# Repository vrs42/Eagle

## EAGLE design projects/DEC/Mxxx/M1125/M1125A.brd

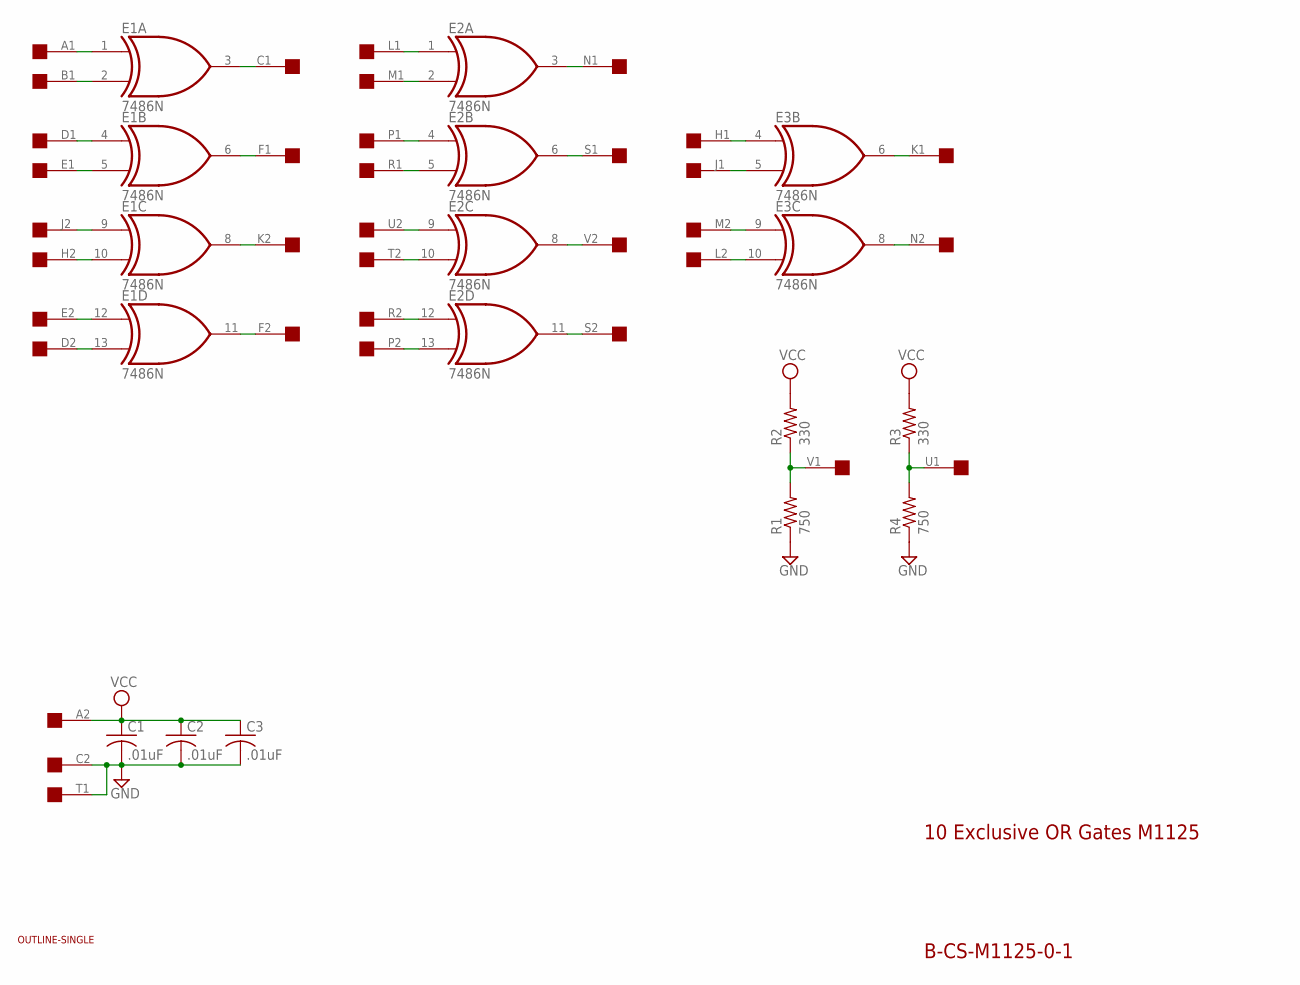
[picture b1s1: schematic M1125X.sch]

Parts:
C1, C2, C3: .01uF; C075-032X103
E1, E2, E3: 7486N; DIL14
R1, R4: 750; 0207/10
R2, R3: 330; 0207/10
U$1: OUTLINE-SINGLE; SINGLE
U$2: SINGLE; EDGE-CON2

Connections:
GND: C1.2, C2.2, C3.2, E1.7 (GND), E2.7 (GND), E3.7 (GND), R1.1, R4.1, U$2.C2, U$2.T1
unnamed: E2.9 (I0), U$2.U2
unnamed: E2.10 (I1), U$2.T2
unnamed: E2.12 (I0), U$2.R2
unnamed: E2.13 (I1), U$2.P2
unnamed: E2.11 (O), U$2.S2
unnamed: E2.8 (O), U$2.V2
unnamed: E1.13 (I1), U$2.D2
unnamed: E1.12 (I0), U$2.E2
unnamed: E1.10 (I1), U$2.H2
unnamed: E1.9 (I0), U$2.J2
unnamed: E1.8 (O), U$2.K2
unnamed: E1.11 (O), U$2.F2
unnamed: E3.10 (I1), U$2.L2
unnamed: E3.9 (I0), U$2.M2
unnamed: E3.8 (O), U$2.N2
unnamed: R1.2, R2.1, U$2.V1
unnamed: R3.1, R4.2, U$2.U1
unnamed: E1.2 (I1), U$2.B1
unnamed: E1.1 (I0), U$2.A1
unnamed: E1.3 (O), U$2.C1
unnamed: E1.6 (O), U$2.F1
unnamed: E1.4 (I0), U$2.D1
unnamed: E1.5 (I1), U$2.E1
unnamed: E3.5 (I1), U$2.J1
unnamed: E3.4 (I0), U$2.H1
unnamed: E3.6 (O), U$2.K1
unnamed: E2.6 (O), U$2.S1
unnamed: E2.3 (O), U$2.N1
unnamed: E2.1 (I0), U$2.L1
unnamed: E2.2 (I1), U$2.M1
unnamed: E2.4 (I0), U$2.P1
unnamed: E2.5 (I1), U$2.R1
VCC: C1.1, C2.1, C3.1, E1.14 (VCC), E2.14 (VCC), E3.14 (VCC), R2.2, R3.2, U$2.A2

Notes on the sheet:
10 Exclusive OR Gates M1125
B-CS-M1125-0-1

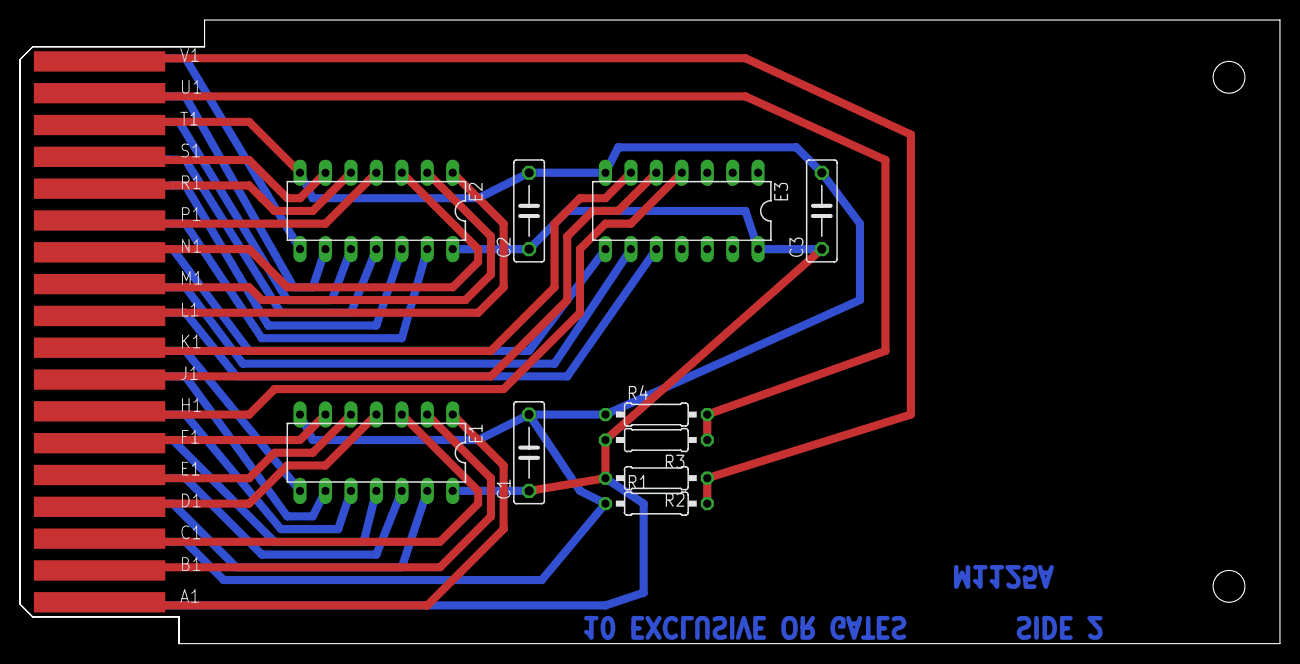
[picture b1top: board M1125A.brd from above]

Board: 2 copper layers, 125.7 x 62.2 mm, 12 parts (0 on the bottom side), 34 nets.

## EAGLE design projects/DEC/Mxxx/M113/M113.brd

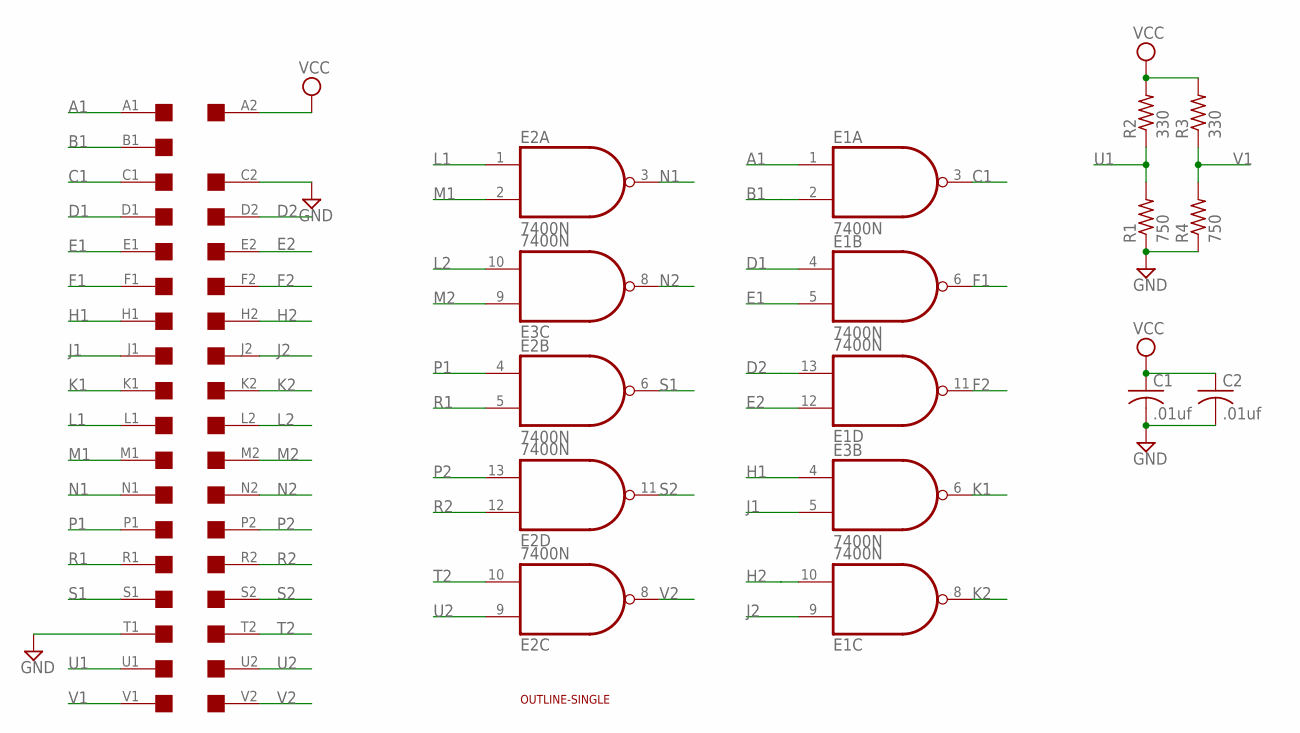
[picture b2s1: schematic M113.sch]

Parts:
C1, C2: .01uf; C050-025X075
E1, E2, E3: 7400N; DIL14
R1, R4: 750; 0207/10
R2, R3: 330; 0207/10
U$1: SINGLE; EDGE-CON2
U$2: OUTLINE-SINGLE; SINGLE

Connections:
A1: E1.1 (I0), U$1.A1
B1: E1.2 (I1), U$1.B1
C1: E1.3 (O), U$1.C1
D1: E1.4 (I0), U$1.D1
D2: E1.13 (I1), U$1.D2
E1: E1.5 (I1), U$1.E1
E2: E1.12 (I0), U$1.E2
F1: E1.6 (O), U$1.F1
F2: E1.11 (O), U$1.F2
GND: C1.2, C2.2, E1.7 (GND), E2.7 (GND), E3.7 (GND), R1.1, R4.1, U$1.C2, U$1.T1
H1: E3.4 (I0), U$1.H1
H2: E1.10 (I1), U$1.H2
J1: E3.5 (I1), U$1.J1
J2: E1.9 (I0), U$1.J2
K1: E3.6 (O), U$1.K1
K2: E1.8 (O), U$1.K2
L1: E2.1 (I0), U$1.L1
L2: E3.10 (I1), U$1.L2
M1: E2.2 (I1), U$1.M1
M2: E3.9 (I0), U$1.M2
N1: E2.3 (O), U$1.N1
N2: E3.8 (O), U$1.N2
P1: E2.4 (I0), U$1.P1
P2: E2.13 (I1), U$1.P2
R1: E2.5 (I1), U$1.R1
R2: E2.12 (I0), U$1.R2
S1: E2.6 (O), U$1.S1
S2: E2.11 (O), U$1.S2
T2: E2.10 (I1), U$1.T2
U1: R1.2, R2.1, U$1.U1
U2: E2.9 (I0), U$1.U2
V1: R3.1, R4.2, U$1.V1
V2: E2.8 (O), U$1.V2
VCC: C1.1, C2.1, E1.14 (VCC), E2.14 (VCC), E3.14 (VCC), R2.2, R3.2, U$1.A2

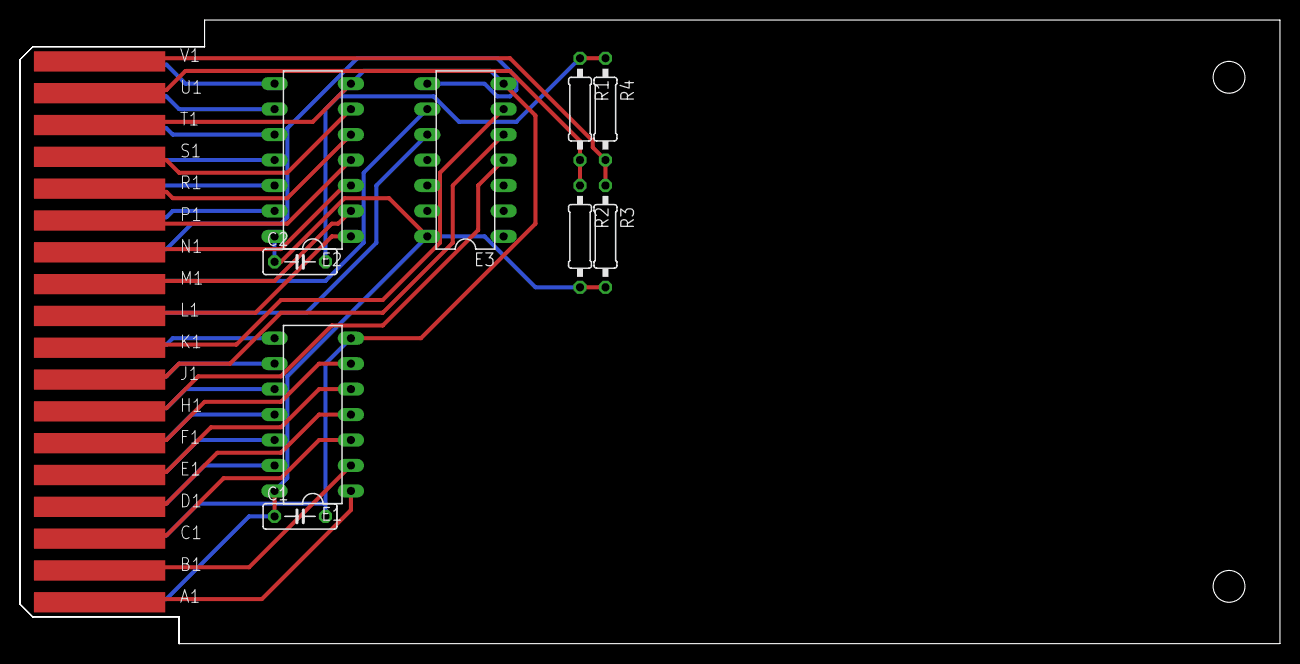
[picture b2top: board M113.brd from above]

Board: 2 copper layers, 125.7 x 62.2 mm, 11 parts (0 on the bottom side), 34 nets.

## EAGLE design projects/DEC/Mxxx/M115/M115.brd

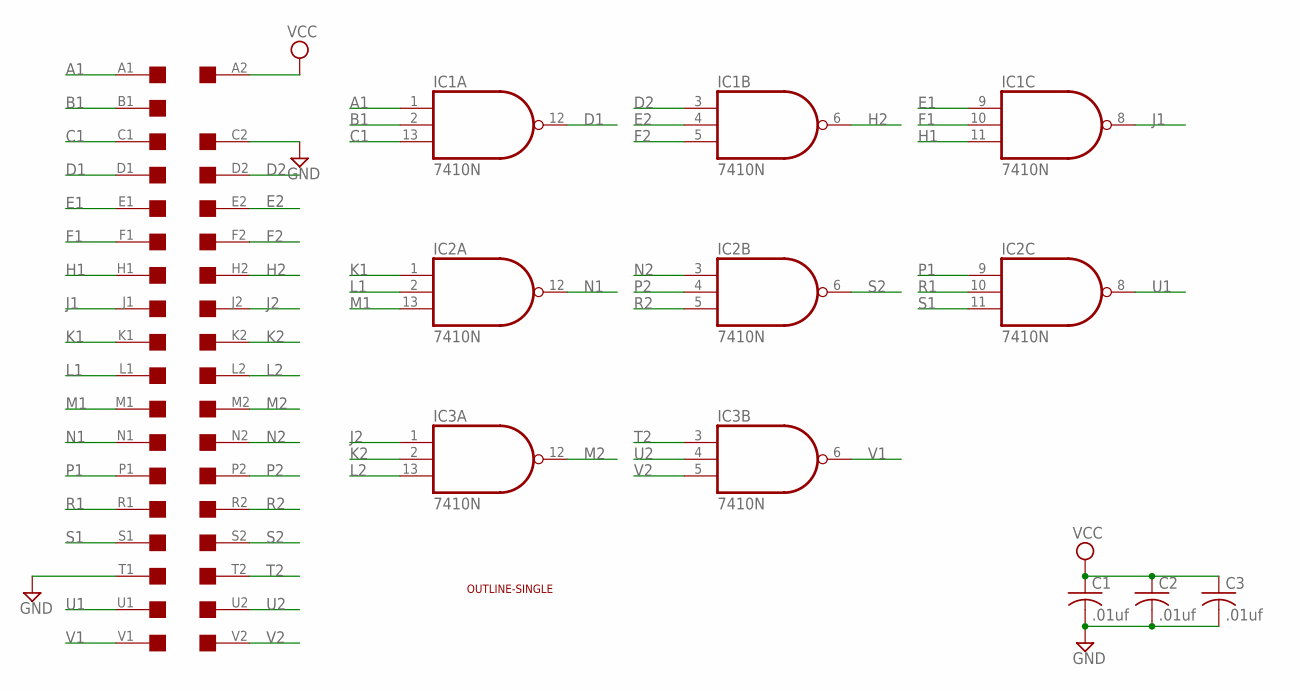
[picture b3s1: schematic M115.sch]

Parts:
C1, C2, C3: .01uf; C050-025X075
IC1, IC2, IC3: 7410N; DIL14
U$1: SINGLE; EDGE-CON2
U$4: OUTLINE-SINGLE; SINGLE

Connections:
A1: IC1.1 (I0), U$1.A1
B1: IC1.2 (I1), U$1.B1
C1: IC1.13 (I2), U$1.C1
D1: IC1.12 (O), U$1.D1
D2: IC1.3 (I0), U$1.D2
E1: IC1.9 (I0), U$1.E1
E2: IC1.4 (I1), U$1.E2
F1: IC1.10 (I1), U$1.F1
F2: IC1.5 (I2), U$1.F2
GND: C1.2, C2.2, C3.2, IC1.7 (GND), IC2.7 (GND), IC3.7 (GND), U$1.C2, U$1.T1
H1: IC1.11 (I2), U$1.H1
H2: IC1.6 (O), U$1.H2
J1: IC1.8 (O), U$1.J1
J2: IC3.1 (I0), U$1.J2
K1: IC2.1 (I0), U$1.K1
K2: IC3.2 (I1), U$1.K2
L1: IC2.2 (I1), U$1.L1
L2: IC3.13 (I2), U$1.L2
M1: IC2.13 (I2), U$1.M1
M2: IC3.12 (O), U$1.M2
N1: IC2.12 (O), U$1.N1
N2: IC2.3 (I0), U$1.N2
P1: IC2.9 (I0), U$1.P1
P2: IC2.4 (I1), U$1.P2
R1: IC2.10 (I1), U$1.R1
R2: IC2.5 (I2), U$1.R2
S1: IC2.11 (I2), U$1.S1
S2: IC2.6 (O), U$1.S2
T2: IC3.3 (I0), U$1.T2
U1: IC2.8 (O), U$1.U1
U2: IC3.4 (I1), U$1.U2
V1: IC3.6 (O), U$1.V1
V2: IC3.5 (I2), U$1.V2
VCC: C1.1, C2.1, C3.1, IC1.14 (VCC), IC2.14 (VCC), IC3.14 (VCC), U$1.A2

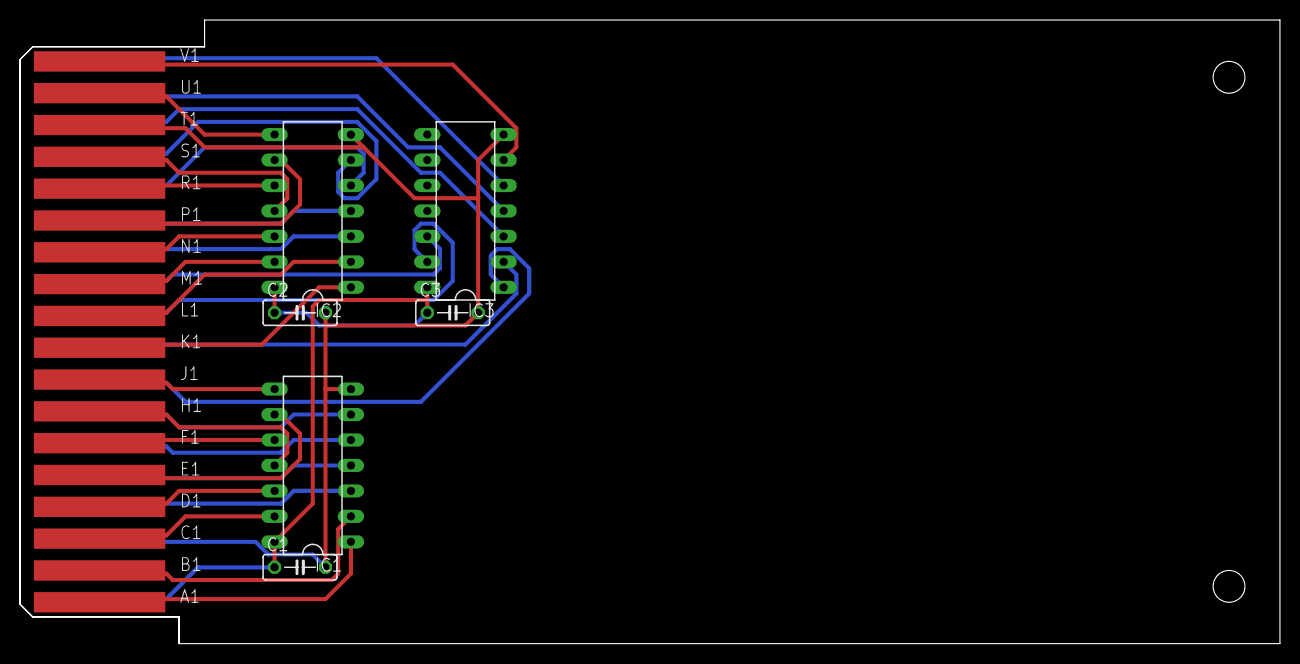
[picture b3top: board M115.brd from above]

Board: 2 copper layers, 125.7 x 62.2 mm, 8 parts (0 on the bottom side), 34 nets.

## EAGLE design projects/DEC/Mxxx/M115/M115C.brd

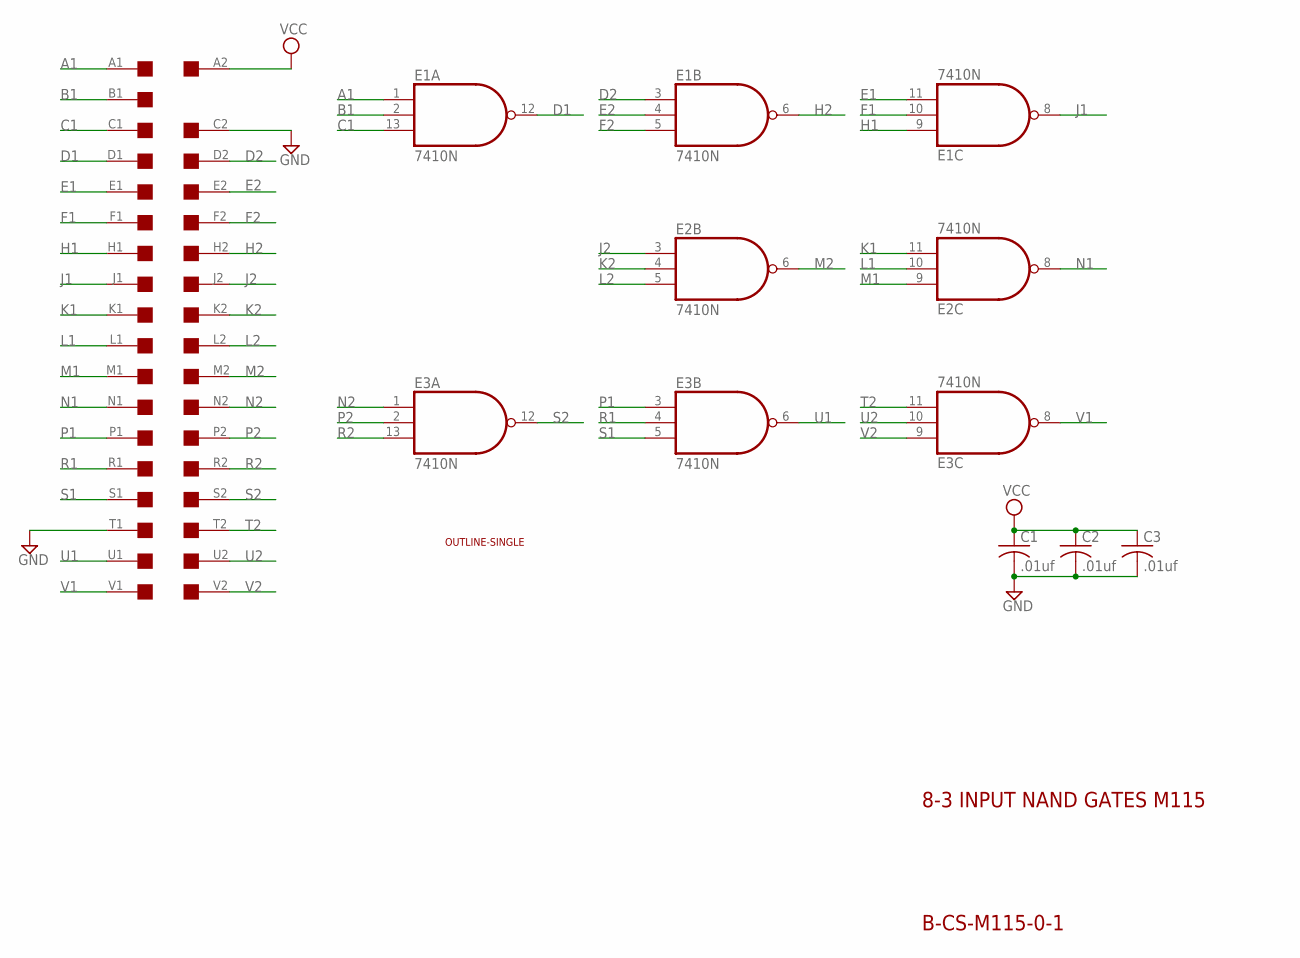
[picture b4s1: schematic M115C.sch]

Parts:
C1, C2, C3: .01uf; C050-025X075
E1, E2, E3: 7410N; DIL14
U$1: SINGLE; EDGE-CON2
U$4: OUTLINE-SINGLE; SINGLE

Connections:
A1: E1.1 (I0), U$1.A1
B1: E1.2 (I1), U$1.B1
C1: E1.13 (I2), U$1.C1
D1: E1.12 (O), U$1.D1
D2: E1.3 (I0), U$1.D2
E1: E1.11 (I2), U$1.E1
E2: E1.4 (I1), U$1.E2
F1: E1.10 (I1), U$1.F1
F2: E1.5 (I2), U$1.F2
GND: C1.2, C2.2, C3.2, E1.7 (GND), E2.7 (GND), E3.7 (GND), U$1.C2, U$1.T1
H1: E1.9 (I0), U$1.H1
H2: E1.6 (O), U$1.H2
J1: E1.8 (O), U$1.J1
J2: E2.3 (I0), U$1.J2
K1: E2.11 (I2), U$1.K1
K2: E2.4 (I1), U$1.K2
L1: E2.10 (I1), U$1.L1
L2: E2.5 (I2), U$1.L2
M1: E2.9 (I0), U$1.M1
M2: E2.6 (O), U$1.M2
N1: E2.8 (O), U$1.N1
N2: E3.1 (I0), U$1.N2
P1: E3.3 (I0), U$1.P1
P2: E3.2 (I1), U$1.P2
R1: E3.4 (I1), U$1.R1
R2: E3.13 (I2), U$1.R2
S1: E3.5 (I2), U$1.S1
S2: E3.12 (O), U$1.S2
T2: E3.11 (I2), U$1.T2
U1: E3.6 (O), U$1.U1
U2: E3.10 (I1), U$1.U2
V1: E3.8 (O), U$1.V1
V2: E3.9 (I0), U$1.V2
VCC: C1.1, C2.1, C3.1, E1.14 (VCC), E2.14 (VCC), E3.14 (VCC), U$1.A2

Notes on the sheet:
8-3 INPUT NAND GATES M115
B-CS-M115-0-1

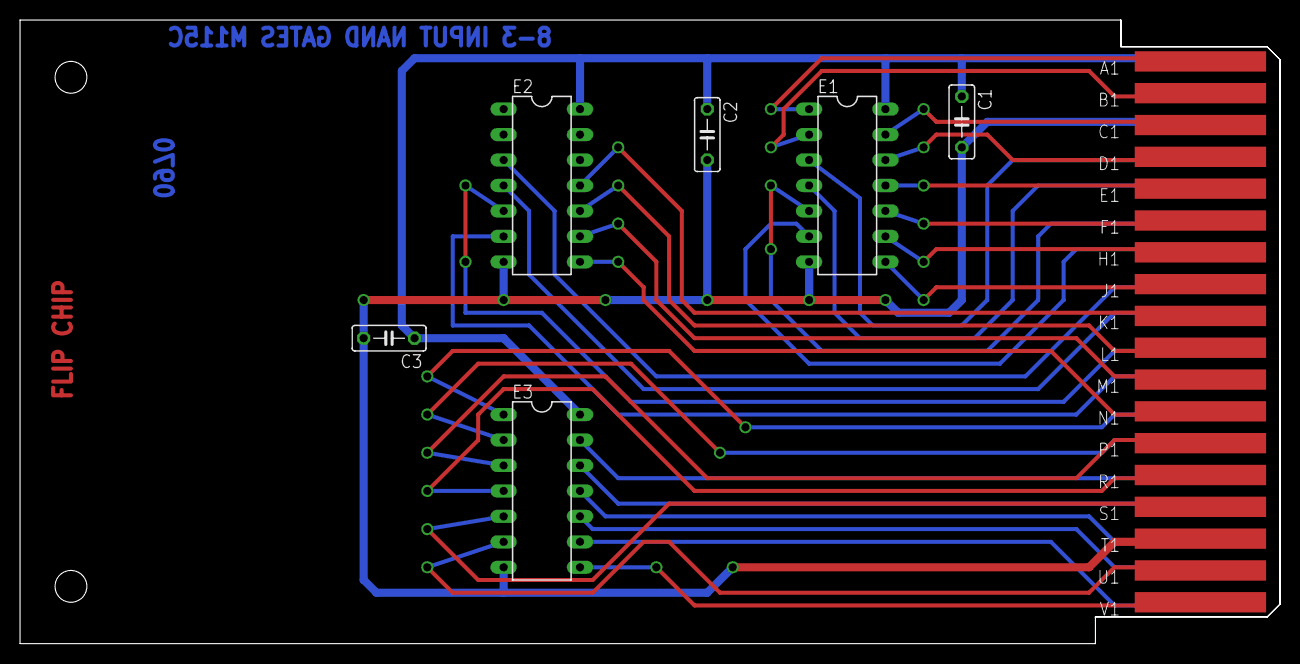
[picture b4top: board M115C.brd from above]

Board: 2 copper layers, 125.7 x 62.2 mm, 8 parts (0 on the bottom side), 34 nets.
